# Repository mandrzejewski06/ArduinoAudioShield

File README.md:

# ArduinoAudioShield
Arduino audio shield project in KiCAD

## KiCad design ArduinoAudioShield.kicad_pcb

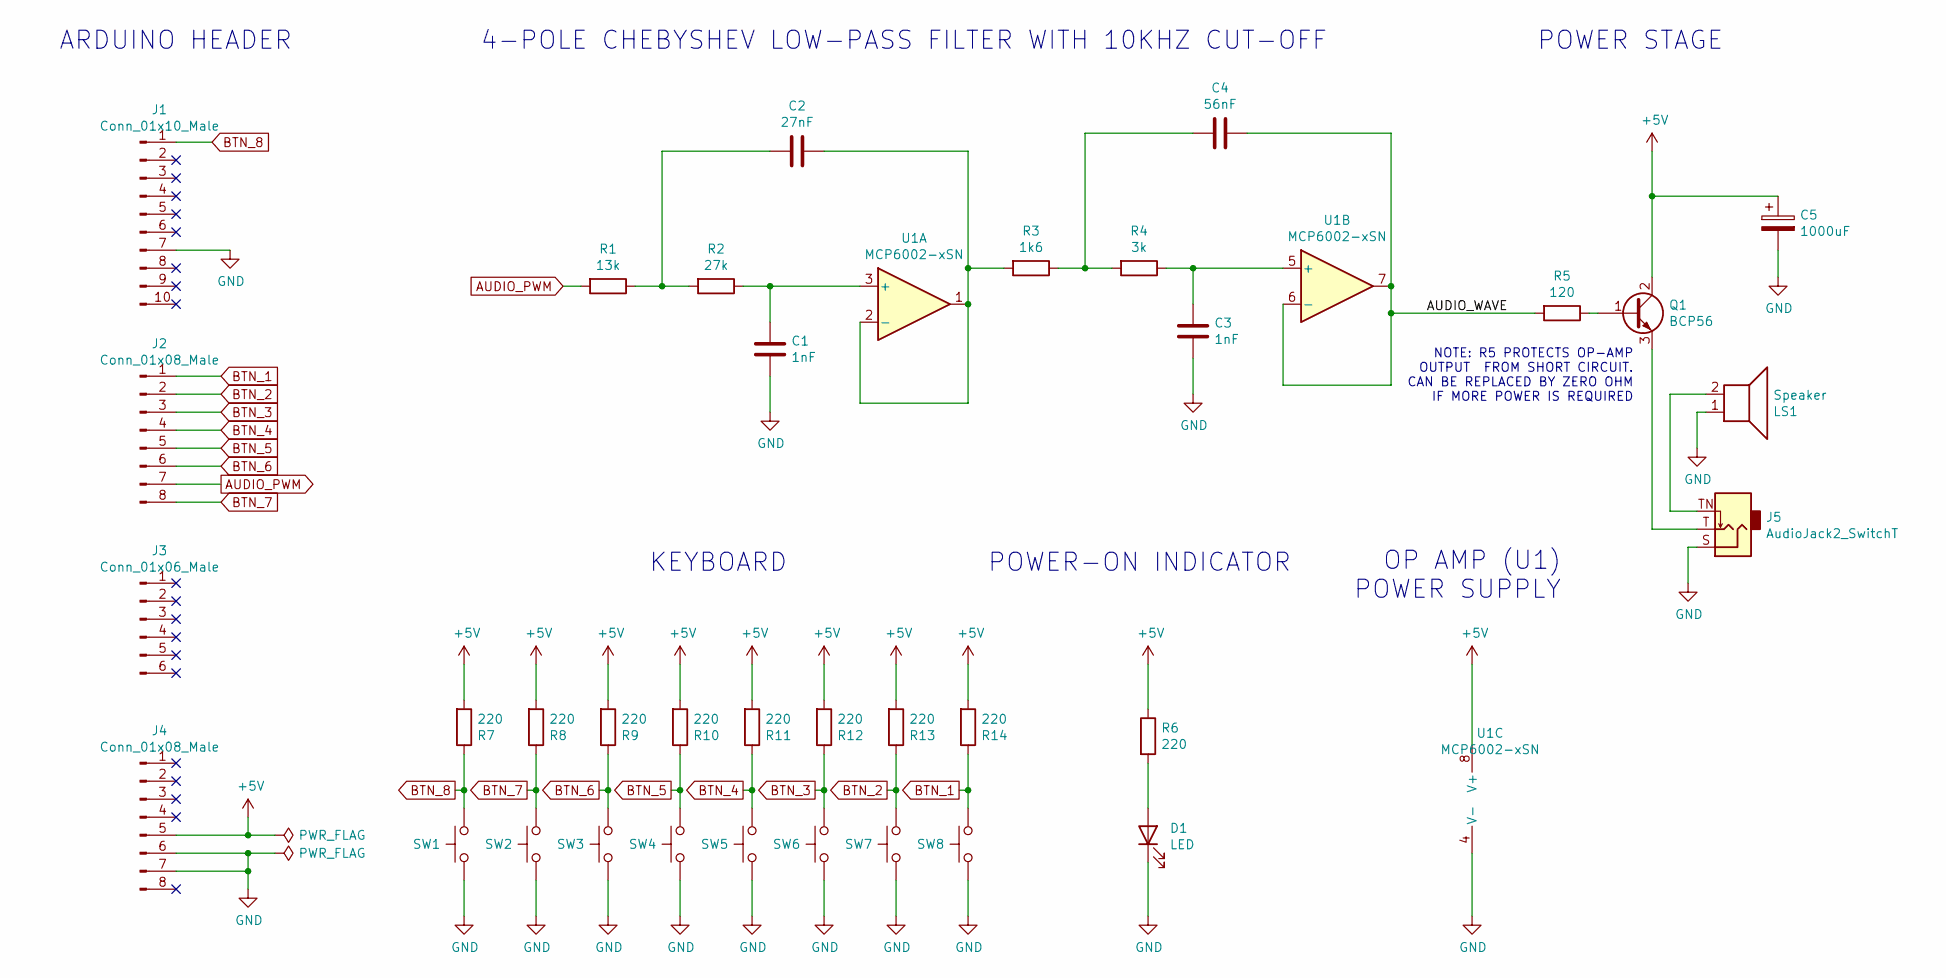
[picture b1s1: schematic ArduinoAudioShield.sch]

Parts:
C1, C3: 1nF; C_0805_2012Metric_Pad1.18x1.45mm_HandSolder
C2: 27nF; C_0805_2012Metric_Pad1.18x1.45mm_HandSolder
C4: 56nF; C_0805_2012Metric_Pad1.18x1.45mm_HandSolder
C5: 1000uF; CP_Elec_10x10
D1: LED; LED_0805_2012Metric_Pad1.15x1.40mm_HandSolder
J1: Conn_01x10_Male; PinHeader_1x10_P2.54mm_Vertical
J2, J4: Conn_01x08_Male; PinHeader_1x08_P2.54mm_Vertical
J3: Conn_01x06_Male; PinHeader_1x06_P2.54mm_Vertical
J5: AudioJack2_SwitchT; Jack_3.5mm_Lumberg_150306_Horizontal
LS1: Speaker; TerminalBlock_Altech_AK300-2_P5.00mm
Q1: BCP56; SOT-223-3_TabPin2
R1: 13k; R_0805_2012Metric_Pad1.20x1.40mm_HandSolder
R2: 27k; R_0805_2012Metric_Pad1.20x1.40mm_HandSolder
R3: 1k6; R_0805_2012Metric_Pad1.20x1.40mm_HandSolder
R4: 3k; R_0805_2012Metric_Pad1.20x1.40mm_HandSolder
R5: 120; R_0805_2012Metric_Pad1.20x1.40mm_HandSolder
R6, R7, R8, R9, R10, R11, R12, R13, R14: 220; R_0805_2012Metric_Pad1.20x1.40mm_HandSolder
SW1, SW2, SW3, SW4, SW5, SW6, SW7, SW8: SWITCH; SW_PUSH_6mm_H5mm
U1: MCP6002-xSN; SOIC-8-1EP_3.9x4.9mm_P1.27mm_EP2.514x3.2mm

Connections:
+5V: C5.1, J4.5, Q1.2 (C), R6.1, R7.2, R8.2, R9.2, R10.2, R11.2, R12.2, R13.2, R14.2, U1.8 (V+)
/AUDIO_WAVE: C4.1, R5.2, U1.6 (-), U1.7
AUDIO_PWM: J2.7, R1.2
BTN_1: J2.1, R14.1, SW8.2 (B)
BTN_2: J2.2, R13.1, SW7.2 (B)
BTN_3: J2.3, R12.1, SW6.2 (B)
BTN_4: J2.4, R11.1, SW5.2 (B)
BTN_5: J2.5, R10.1, SW4.2 (B)
BTN_6: J2.6, R9.1, SW3.2 (B)
BTN_7: J2.8, R8.1, SW2.2 (B)
BTN_8: J1.1, R7.1, SW1.2 (B)
GND: C1.2, C3.2, C5.2, D1.1 (K), J1.7, J4.6, J4.7, J5.S, LS1.1, SW1.1 (A), SW2.1 (A), SW3.1 (A), SW4.1 (A), SW5.1 (A), SW6.1 (A), SW7.1 (A), SW8.1 (A), U1.4 (V-)
unnamed: C1.1, R2.1, U1.3 (+)
unnamed: C2.1, R3.2, U1.1, U1.2 (-)
unnamed: C2.2, R1.1, R2.2
unnamed: C3.1, R4.1, U1.5 (+)
unnamed: C4.2, R3.1, R4.2
unnamed: D1.2 (A), R6.2
unnamed: J5.T, Q1.3 (E)
unnamed: J5.TN, LS1.2
unnamed: Q1.1 (B), R5.1

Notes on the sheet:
ARDUINO HEADER
4-POLE CHEBYSHEV LOW-PASS FILTER WITH 10KHZ CUT-OFF
POWER STAGE
KEYBOARD
POWER-ON INDICATOR
OP AMP (U1) POWER SUPPLY
NOTE: R5 PROTECTS OP-AMP OUTPUT FROM SHORT CIRCUIT. CAN BE REPLACED BY ZERO OHM IF MORE POWER IS REQUIRED

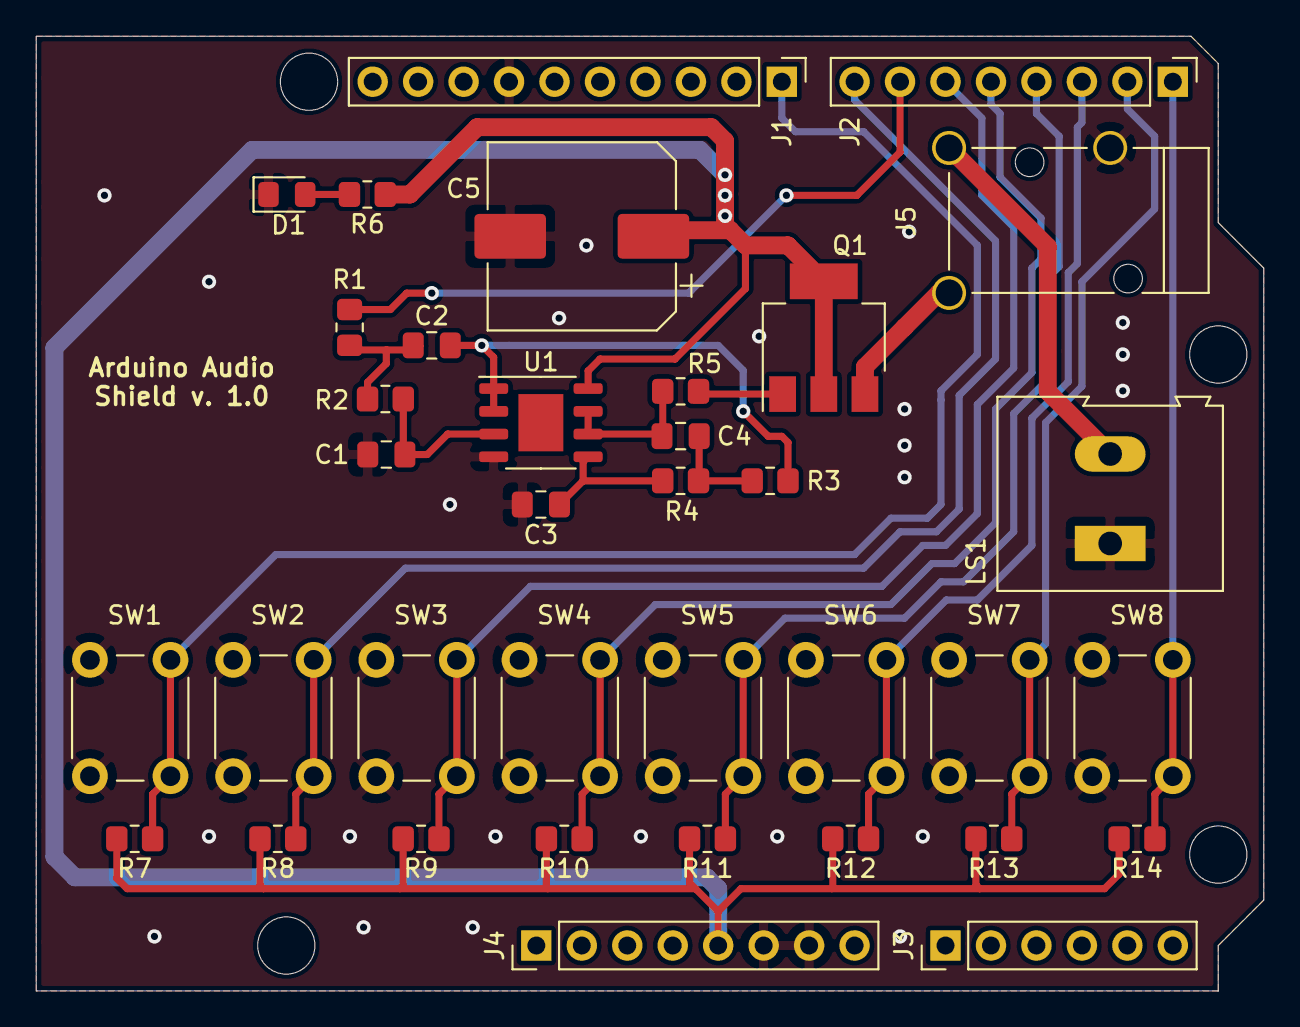
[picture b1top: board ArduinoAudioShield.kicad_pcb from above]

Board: 2 copper layers, 68.6 x 53.3 mm, 36 parts (0 on the bottom side), 21 nets.

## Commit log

2022-01-16 Audio shield all files
2022-01-16 Added image of the board
